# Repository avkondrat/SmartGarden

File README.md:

This low cost kit for creating battery low power sensors(device) and a gateway for wireless (based on the NRF24) monitoring of soil condition with WiFi data transmission to the IOT platform.

Included controller's firmware files, circuits and boards, case models for 3D printing. No programming required for customization.

Please, read WiKi (RUS) project https://github.com/avkondrat/SmartGarden/wiki

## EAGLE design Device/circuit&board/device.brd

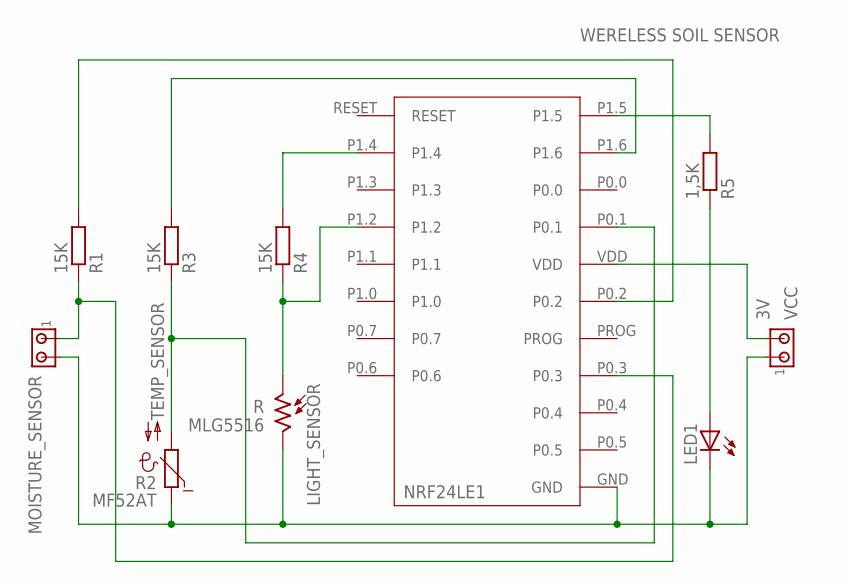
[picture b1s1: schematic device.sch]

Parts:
LED1: LEDCHIP-LED0805; CHIP-LED0805
MOISTURE_SENSOR: MTA02-100; 10X02MTA
NRF: NRF24LE1
R: MLG5516; T0-46-A10XX
R1, R3, R4: 15K; R1206
R2: MF52AT; P640
R5: 1,5K; R1206
VCC: 3V; 10X02MTA

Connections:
GND: LED1.C, MOISTURE_SENSOR.2, NRF.GND, R.2, R2.1, VCC.1
H: MOISTURE_SENSOR.1, NRF.P0.3, R1.1
H_V: NRF.P0.2, R1.2
L: NRF.P1.2, R.1, R4.1
LED: NRF.P1.5, R5.2
L_V: NRF.P1.4, R4.2
unnamed: LED1.A, R5.1
T: NRF.P0.1, R2.2, R3.1
T_V: NRF.P1.6, R3.2
VDD: NRF.VDD, VCC.2

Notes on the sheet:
NRF24LE1
LIGHT_SENSOR
TEMP_SENSOR
WERELESS SOIL SENSOR

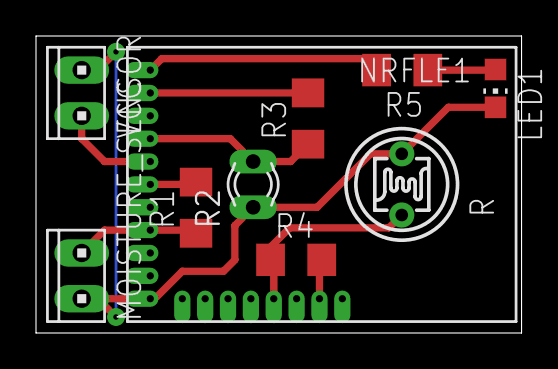
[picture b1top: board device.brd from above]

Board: 2 copper layers, 27.0 x 16.5 mm, 10 parts (0 on the bottom side), 10 nets.

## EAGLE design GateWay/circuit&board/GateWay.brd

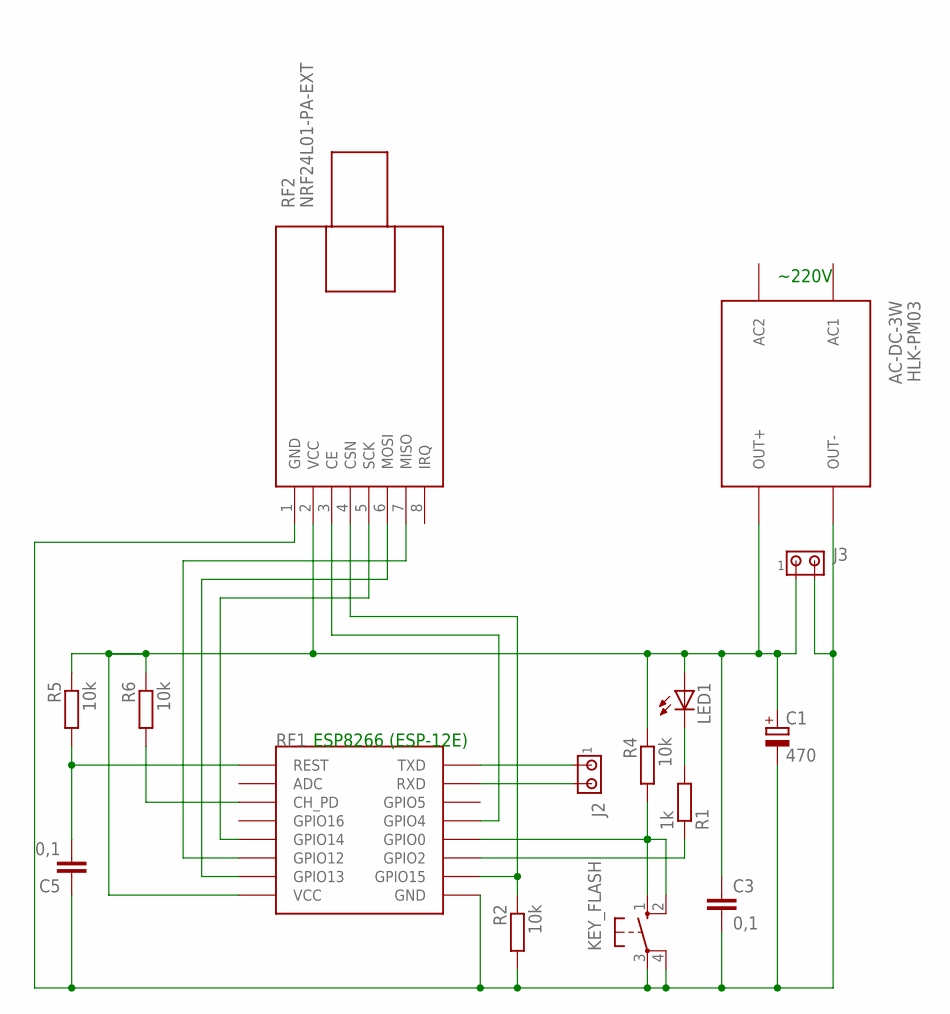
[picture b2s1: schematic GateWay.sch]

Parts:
C1: 470; E2,5-6E
C3: 0,1; C025-024X044
C5: 0,1; C025-025X050
HLK-PM03: AC-DC-3W; AC-DC-3.5W
J2, J3: MTA02-100; 10X02MTA
KEY_FLASH: 10-XX; B3F-10XX
LED1: LED5MM
R1: 1k; 0204/7
R2, R4: 10k; 0204/7
R5: 10k; 0207/12
R6: 10k; 0207/10
RF1: ESP; ESP12E-SMD
RF2: NRF24L01-PA-EXT; WIRELESS-NRF24L01-PA-EXT

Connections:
CHS: R6.2, RF1.CH_PD
FLASH: KEY_FLASH.1 (S), KEY_FLASH.2 (S1), R4.2, RF1.GPIO0
GND: C1.-, C3.2, C5.1, HLK-PM03.J2.1 (OUT-), J3.2, KEY_FLASH.3, KEY_FLASH.4 (P1), R2.2, RF1.GND, RF2.1 (GND)
GPIO4: RF1.GPIO4, RF2.3 (CE)
GPIO12: RF1.GPIO12, RF2.7 (MISO)
GPIO13: RF1.GPIO13, RF2.6 (MOSI)
GPIO14: RF1.GPIO14, RF2.5 (SCK)
GPIO15: R2.1, RF1.GPIO15, RF2.4 (CSN)
LED: R1.1, RF1.GPIO2
unnamed: LED1.K (C), R1.2
RESET: C5.2, R5.2, RF1.RESET (REST)
RX: J2.2, RF1.RXD0 (RXD)
TX: J2.1, RF1.TXD0 (TXD)
VCC: C1.+, C3.1, HLK-PM03.J2.3 (OUT+), J3.1, LED1.A, R4.1, R5.1, R6.1, RF1.VCC, RF2.2 (VCC)

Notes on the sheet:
ESP8266 (ESP-12E)
~220V

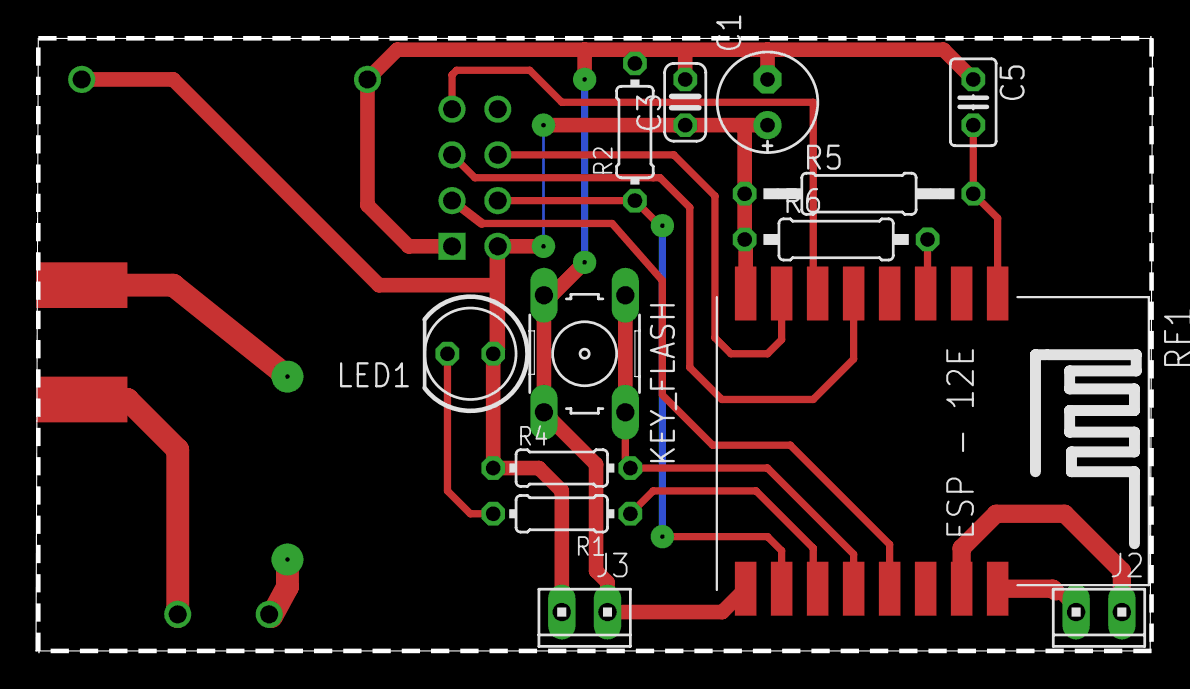
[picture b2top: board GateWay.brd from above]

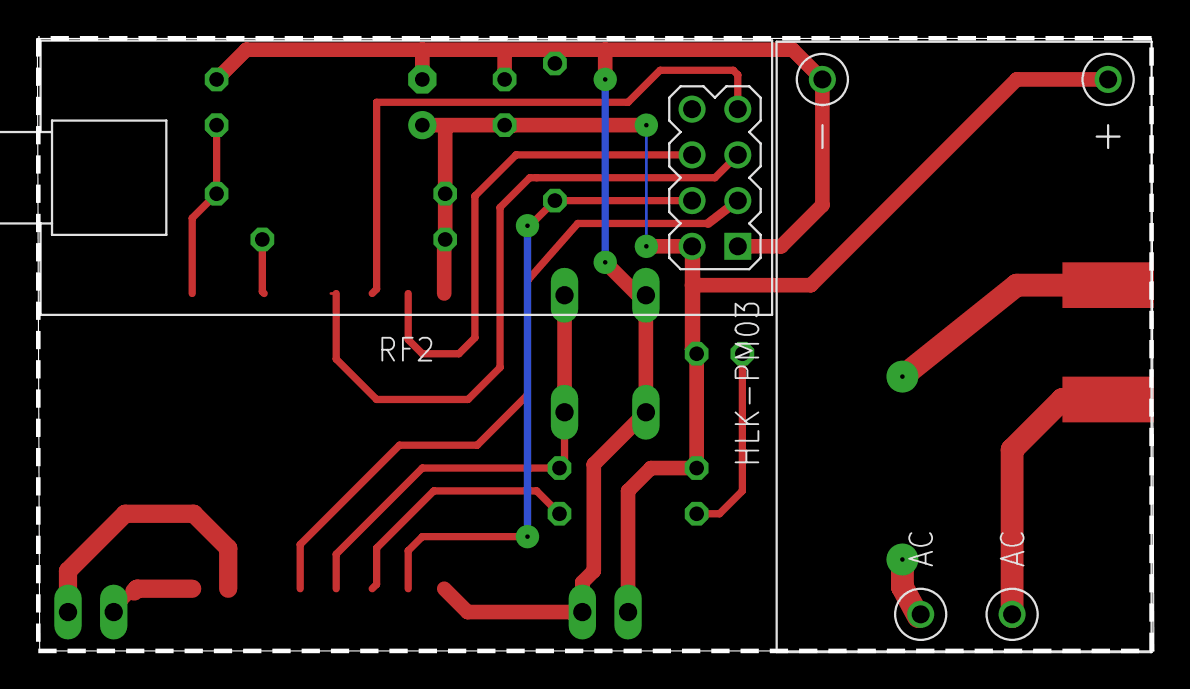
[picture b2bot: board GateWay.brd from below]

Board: 2 copper layers, 61.8 x 34.0 mm, 15 parts (2 on the bottom side), 14 nets.

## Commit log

2019-02-08 structure and data update
2019-02-19 Update GateWay.bin
    For convenience of working with data on the IoT side of the platform, the structure of the JSON message is changed to
    {
    "dN.sBAT": X1,
    "dN.sA0": X2,
    "dN.sA1": X3,
    "dN.sA2": X4,

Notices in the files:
parts and their libraries:
diy-modules: Released under the Creative Commons Attribution 4.0 International License: http://creativecommons.org/licenses/by/4.0
